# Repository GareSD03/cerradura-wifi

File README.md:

# cerradura-wifi
Proyecto Placa PCB
Presentación de proyecto Placa PCB en EAGLE
Tyler Rojas
Edgard Yáñez

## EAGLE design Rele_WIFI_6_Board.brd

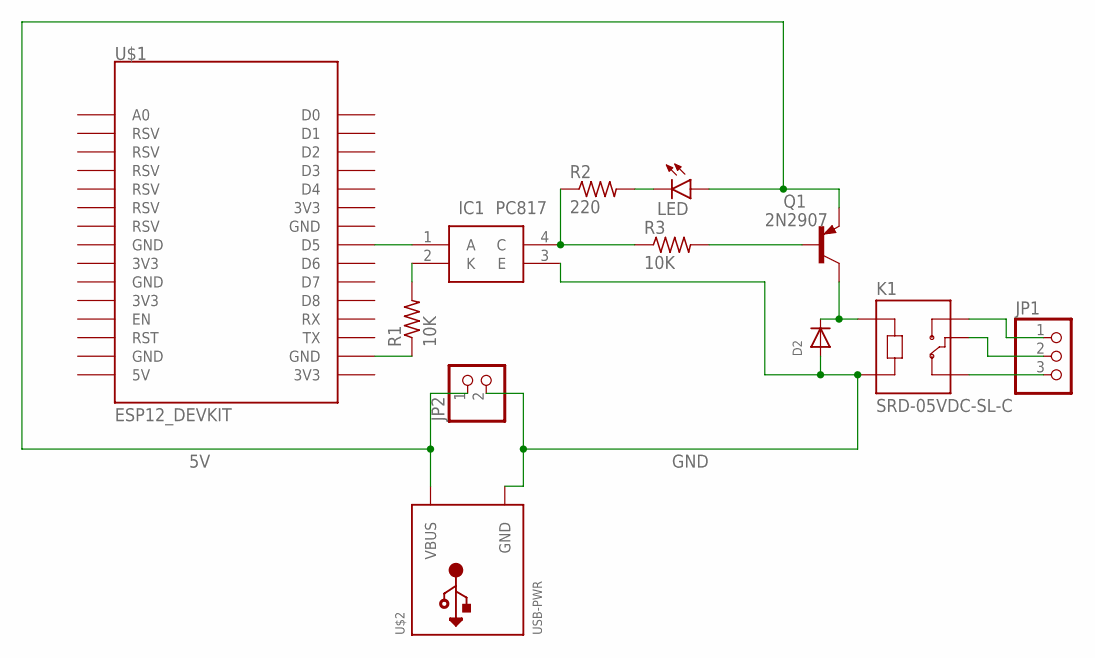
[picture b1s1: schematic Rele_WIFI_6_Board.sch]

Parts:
D2: DIODEDO-1N4148; DO-1N4148
IC1: PC817; DIP810W60P254L460H500Q4N
JP1: PINHD-1X3; 1X03
JP2: PINHD-1X2; 1X02
K1: SRD-05VDC-SL-C; RELAY_SRD-05VDC-SL-C
LED: LED5MM
Q1: 2N2907; TO92-EBC-OVAL
R1, R3: 10K; 0309/12
R2: 220; 0309/12
U$1: ESP12_DEVKIT
U$2: USB-PWR; USB-MINIB-THM-MOLEX-PWRONLY

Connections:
5V: JP2.1, LED.A, Q1.E, U$2.VBUS
GND: D2.A, IC1.3 (E), JP2.2, K1.A2, U$2.GND
unnamed: IC1.1 (A), U$1.D5
unnamed: IC1.4 (C), R2.1, R3.1
unnamed: Q1.B, R3.2
unnamed: IC1.2 (K), R1.2
unnamed: R1.1, U$1.GND@3 (GND)
unnamed: LED.K (C), R2.2
unnamed: D2.C, K1.A1, Q1.C
unnamed: JP1.1, K1.NO
unnamed: JP1.2, K1.COM
unnamed: JP1.3, K1.NC

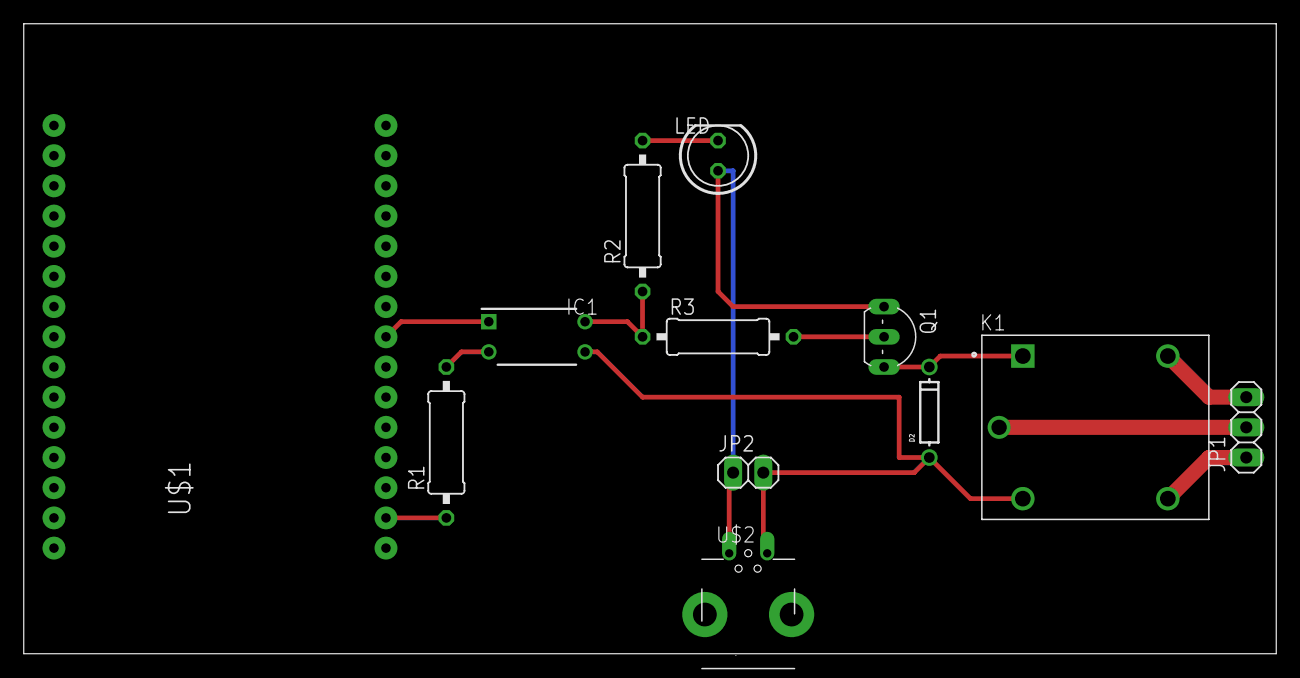
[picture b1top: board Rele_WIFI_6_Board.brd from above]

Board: 2 copper layers, 105.4 x 53.0 mm, 12 parts (0 on the bottom side), 12 nets.

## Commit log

2021-11-25 presentacion
